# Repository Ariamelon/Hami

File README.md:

# Hami
 Simple numberpad with OLED and encoder support, nothing else to say really. Designed for use with a standard 0.91" SSD1306 OLED or the [Crenshaw](https://github.com/Ariamelon/Crenshaw) 1.3" OLED breakout board.

 ## Changelog
 * 27/09/2020: Initial commit.
 * 28/09/2020: Added rotary encoder support.
 * 24/10/2020: Updated to V1.1. Moved position of OLED to allow for enough room and changed design of plate to compensate.

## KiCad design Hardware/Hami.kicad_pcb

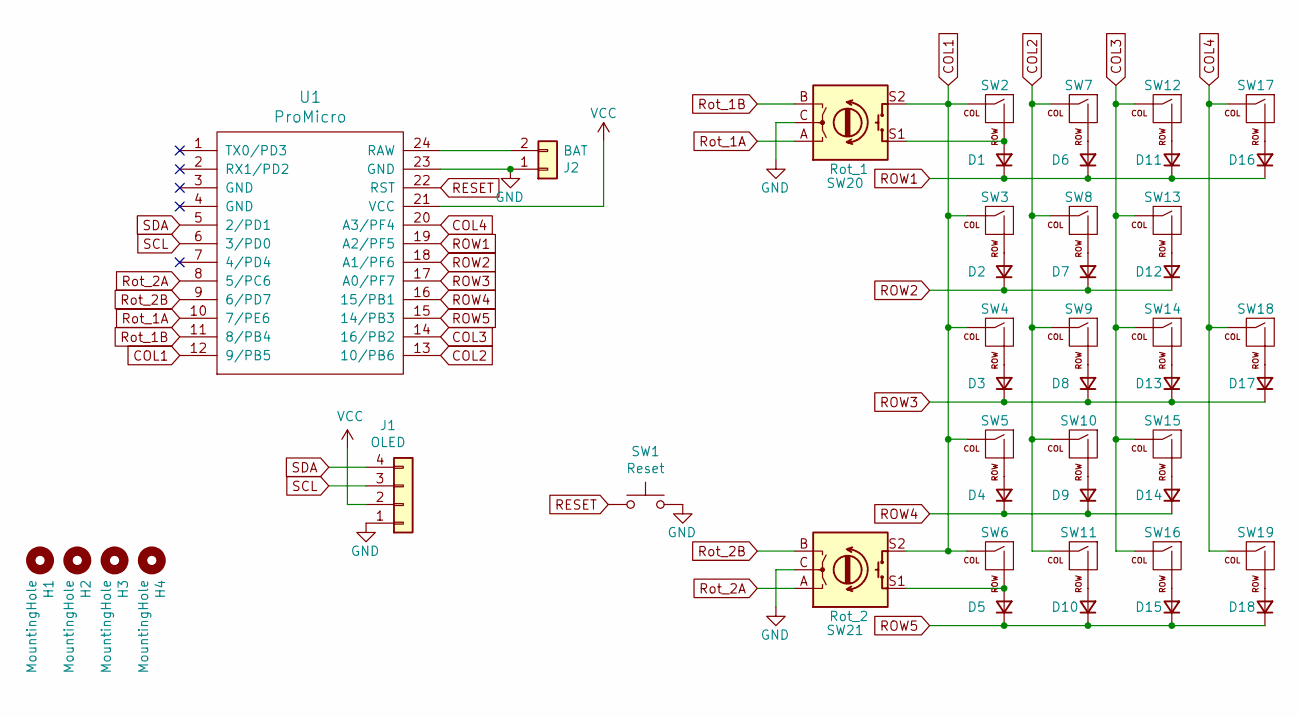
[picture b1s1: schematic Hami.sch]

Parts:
D1, D2, D3, D4, D5, D6, D7, D8, D9, D10, D11, D12, D13, D14, D15, D16, D17, D18: D; D_SOD-123
H1, H2, H3, H4: MountingHole; MountingHole_2.2mm_M2_Pad
J1: OLED; PinHeader_1x04_P2.54mm_Vertical_No_Silk
J2: BAT; Battery_Solder_Points
SW1: Reset; SW_SPST_TL3342
SW2, SW3, SW4, SW5, SW6, SW7, SW8, SW9, SW10, SW11, SW12, SW13, SW14, SW15, SW16, SW17: MX; CherryMX_Hotswap_SMK
SW18, SW19: MX; CherryMX_Hotswap_2u_SMK
SW20: Rot_1; RotaryEncoder_Alps_EC11E-Switch_Vertical_H20mm
SW21: Rot_2; RotaryEncoder_Alps_EC11E-Switch_Vertical_H20mm
U1: ProMicro; ArduinoProMicro_Blank

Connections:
COL1: SW2.1 (COL), SW3.1 (COL), SW4.1 (COL), SW5.1 (COL), SW6.1 (COL), SW20.S2, SW21.S2, U1.12 (9/PB5)
COL2: SW7.1 (COL), SW8.1 (COL), SW9.1 (COL), SW10.1 (COL), SW11.1 (COL), U1.13 (10/PB6)
COL3: SW12.1 (COL), SW13.1 (COL), SW14.1 (COL), SW15.1 (COL), SW16.1 (COL), U1.14 (16/PB2)
COL4: SW17.1 (COL), SW18.1 (COL), SW19.1 (COL), U1.20 (A3/PF4)
GND: J1.1, J2.1, SW1.2, SW20.C, SW21.C, U1.23 (GND)
unnamed: D1.2 (A), SW2.2 (ROW), SW20.S1
unnamed: D2.2 (A), SW3.2 (ROW)
unnamed: D3.2 (A), SW4.2 (ROW)
unnamed: D4.2 (A), SW5.2 (ROW)
unnamed: D5.2 (A), SW6.2 (ROW), SW21.S1
unnamed: D6.2 (A), SW7.2 (ROW)
unnamed: D7.2 (A), SW8.2 (ROW)
unnamed: D8.2 (A), SW9.2 (ROW)
unnamed: D9.2 (A), SW10.2 (ROW)
unnamed: D10.2 (A), SW11.2 (ROW)
unnamed: D11.2 (A), SW12.2 (ROW)
unnamed: D12.2 (A), SW13.2 (ROW)
unnamed: D13.2 (A), SW14.2 (ROW)
unnamed: D14.2 (A), SW15.2 (ROW)
unnamed: D15.2 (A), SW16.2 (ROW)
unnamed: D16.2 (A), SW17.2 (ROW)
unnamed: D17.2 (A), SW18.2 (ROW)
unnamed: D18.2 (A), SW19.2 (ROW)
unnamed: J2.2, U1.24 (RAW)
RESET: SW1.1, U1.22 (RST)
ROW1: D1.1 (K), D6.1 (K), D11.1 (K), D16.1 (K), U1.19 (A2/PF5)
ROW2: D2.1 (K), D7.1 (K), D12.1 (K), U1.18 (A1/PF6)
ROW3: D3.1 (K), D8.1 (K), D13.1 (K), D17.1 (K), U1.17 (A0/PF7)
ROW4: D4.1 (K), D9.1 (K), D14.1 (K), U1.16 (15/PB1)
ROW5: D5.1 (K), D10.1 (K), D15.1 (K), D18.1 (K), U1.15 (14/PB3)
Rot_1A: SW20.A, U1.10 (7/PE6)
Rot_1B: SW20.B, U1.11 (8/PB4)
Rot_2A: SW21.A, U1.8 (5/PC6)
Rot_2B: SW21.B, U1.9 (6/PD7)
SCL: J1.3, U1.6 (3/PD0)
SDA: J1.4, U1.5 (2/PD1)
VCC: J1.2, U1.21 (VCC)

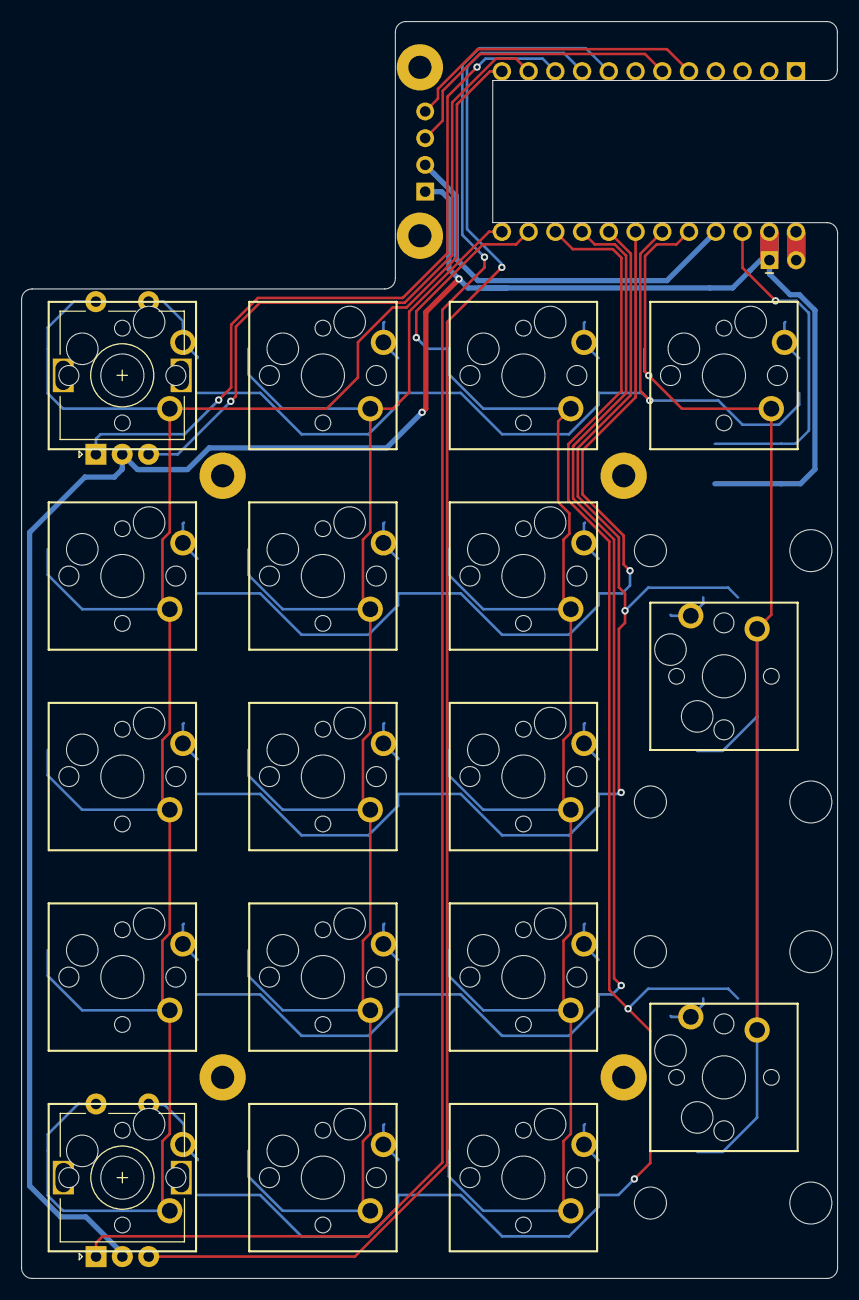
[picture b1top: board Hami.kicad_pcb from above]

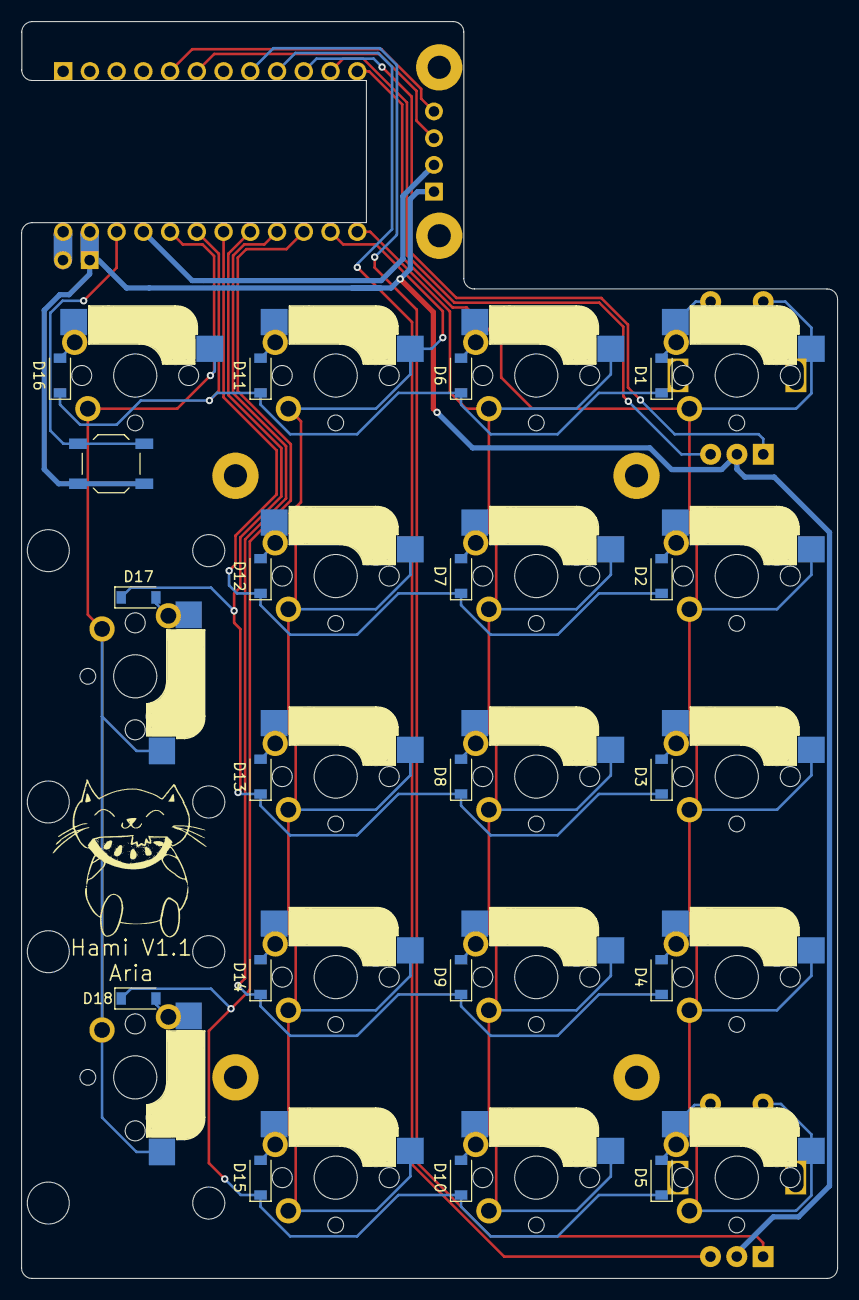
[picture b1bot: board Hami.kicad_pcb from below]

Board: 2 copper layers, 77.5 x 119.4 mm, 46 parts (19 on the bottom side), 37 nets.

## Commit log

2020-09-27 Updated the description
2020-09-28 Hami V1.1
    Because who doesn't need rotary encoder support in the botton and top left corners? Also re-routed some of the traces.
2020-09-28 Proper case files and gerbers
    Added an STL file for a rudimentary 3D-printed case for the Hami as well as DXF and gerber files for a plate.
2020-09-28 Added BOM
2020-09-30 Update LICENSE
2020-10-01 Added renders and updated readme
2020-10-02 Changed footprint references
2020-10-02 Fixed back render
2020-10-24 Moved position of OLED, added new plate
2020-10-24 Fixed image link
2020-10-24 Better render
